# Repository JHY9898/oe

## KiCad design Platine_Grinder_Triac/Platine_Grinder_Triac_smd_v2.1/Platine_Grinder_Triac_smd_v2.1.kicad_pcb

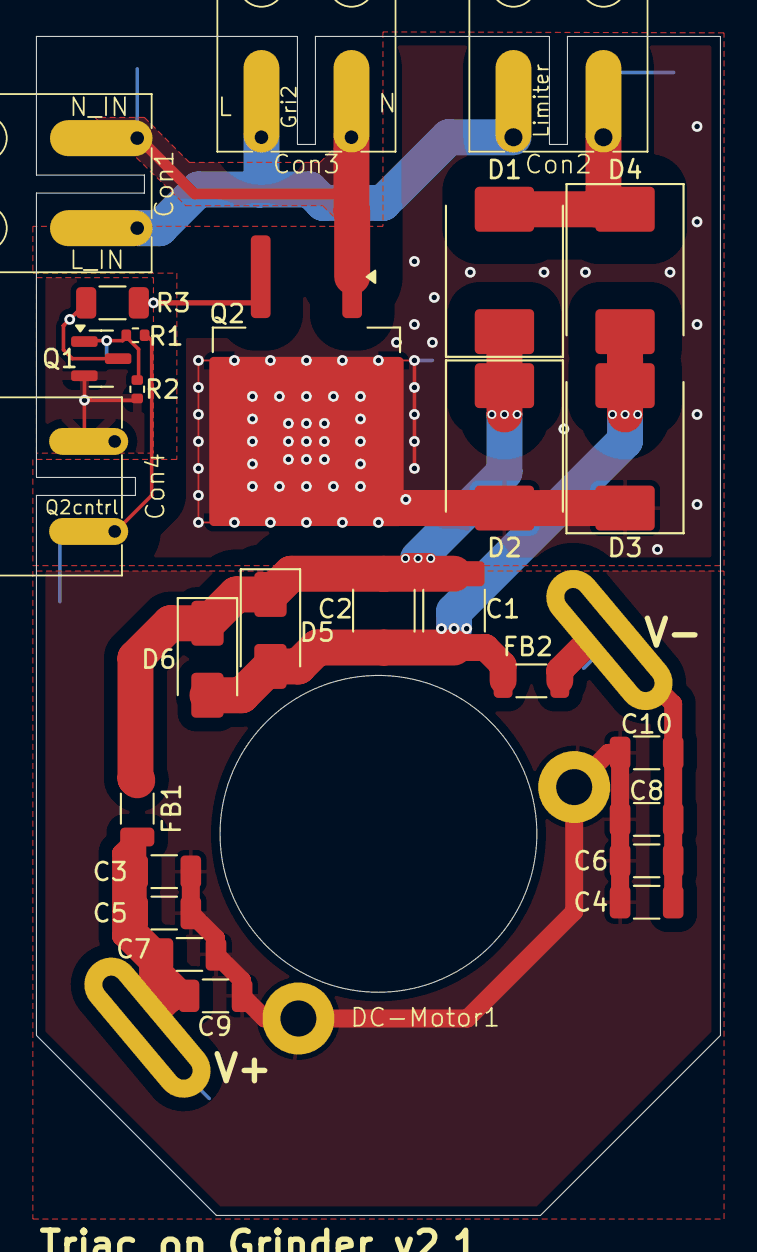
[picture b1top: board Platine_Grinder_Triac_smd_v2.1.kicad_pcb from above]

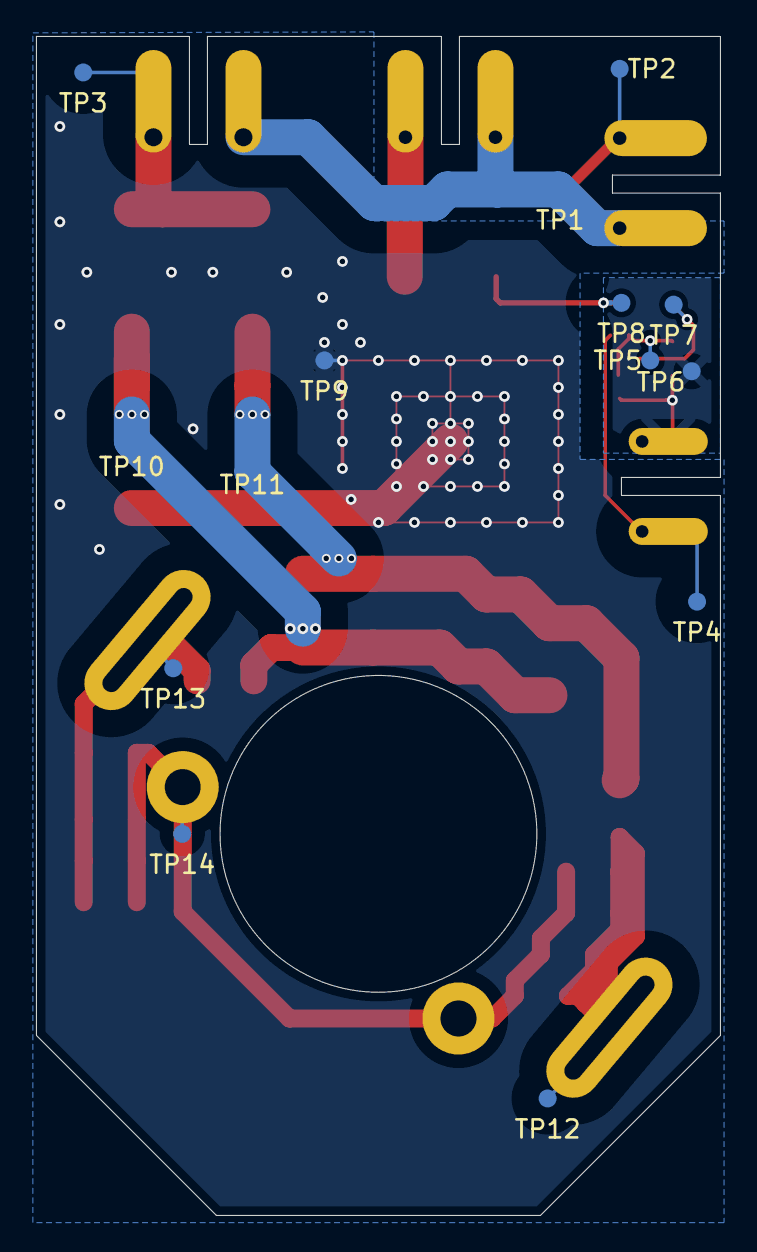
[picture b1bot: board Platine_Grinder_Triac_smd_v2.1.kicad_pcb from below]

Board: 2 copper layers, 38.0 x 65.5 mm, 42 parts (14 on the bottom side), 14 nets.

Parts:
C1: 1nF; C_1812_4532Metric
C2: 100nF; C_1812_4532Metric
C3, C4: 680pF; C_1206_3216Metric
C5, C6: 330pF; C_1206_3216Metric
C7, C8: 100pF; C_1206_3216Metric
C9, C10: 47pF; C_1206_3216Metric
Con1, Con2, Con3: Rast2.5pro; RAST2.5pro_2P
Con4: Rast2.5; RAST2.5_3P_2PADs
D1, D2, D3, D4: S3M; D_SMC
D5, D6: GS1M; D_SMA
DC-Motor1: Grinder
FB1, FB2: FerriteBead_Small; L_1206_3216Metric
Q1: BC847C; SOT-23
Q2: T835H-8G; TO-263-2
R1, R2: 3.3k; R_0402_1005Metric
R3: 47; R_1206_3216Metric
TP1, TP2, TP3, TP4, TP5, TP6, TP7, TP8, TP9, TP10, TP11, TP12, TP13, TP14: TestPoint_D1.0mm; TestPoint_Pad_D1.0mm

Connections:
/L_In: Con1.1 (Con), Con2.1 (Con), Con3.1 (Con), TP1.1
/L_Limiter: Con2.2 (Con), D1.2 (A), D4.1 (K), TP3.1
/N_In: Con1.2 (Con), Con3.2 (Con), Q2.1 (A1), TP2.1
/N_Triac: D2.2 (A), D3.1 (K), Q2.2 (A2), TP9.1
/Net-(Q1-B): Q1.1 (B), R1.2, R2.1, TP5.1
/Net-(Q2-G): Q2.3 (G), R3.2, TP8.1
/Net-Q1-C: Q1.3 (C), R3.1, TP7.1
/Sig_In: Con4.1 (Con), R1.1, TP4.1
/V+: C3.1, C5.1, C7.1, C9.1, DC-Motor1.1 (V+), FB1.2, TP12.1
/V+_Rectifier: C1.1, C2.1, D1.1 (K), D2.1 (K), D5.1 (K), D6.1 (K), FB1.1, TP11.1
/V-: C4.2, C6.2, C8.2, C10.2, DC-Motor1.2 (V-), FB2.2, TP13.1
/V-_Rectifier: C1.2, C2.2, D3.2 (A), D4.2 (A), D5.2 (A), D6.2 (A), FB2.1, TP10.1
/V_Case: C3.2, C4.1, C5.2, C6.1, C7.2, C8.1, C9.2, C10.1, DC-Motor1.3 (Case1), DC-Motor1.4 (Case2), TP14.1
GND: Con4.2 (Con), Q1.2 (E), R2.2, TP6.1

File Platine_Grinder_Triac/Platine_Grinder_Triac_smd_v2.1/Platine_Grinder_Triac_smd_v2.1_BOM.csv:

"Reference","Value","Bauform","Qty","Hersteller"
"C1","1nF","1812","1","FENGHUA"
"C2","100nF","1812","1","MuRata"
"C3,C4","680pF","1206","2","FENGHUA"
"C5,C6","330pF","1206","2","FENGHUA"
"C7,C8","100pF","1206","2","FENGHUA"
"C9,C10","47pF","1206","2","FENGHUA"
"Con1,Con2,Con3","Rast2.5pro","","3",""
"Con4","Rast2.5","","1",""
"D1,D2,D3,D4","S3M","SMC","4","Vishay"
"D5,D6","GS1M","SMA","2","PANJIT"
"DC-Motor1","~","","1",""
"FB1,FB2","FerriteBead_Small","1206","2","Wuerth"
"Q1","BC847C","SOT-23","1","Infineon"
"Q2","T835H-8G","D2PAK","1","ST Microelectronis"
"R1,R2","3.3k","0402","2","Vishay"
"R3","47","1206","1","Vishay"
"TP1,TP2,TP3,TP4,TP5,TP6,TP7,TP8,TP9,TP10,TP11,TP12,TP13,TP14","TestPoint_D1.0mm","D=1mm","14",""
